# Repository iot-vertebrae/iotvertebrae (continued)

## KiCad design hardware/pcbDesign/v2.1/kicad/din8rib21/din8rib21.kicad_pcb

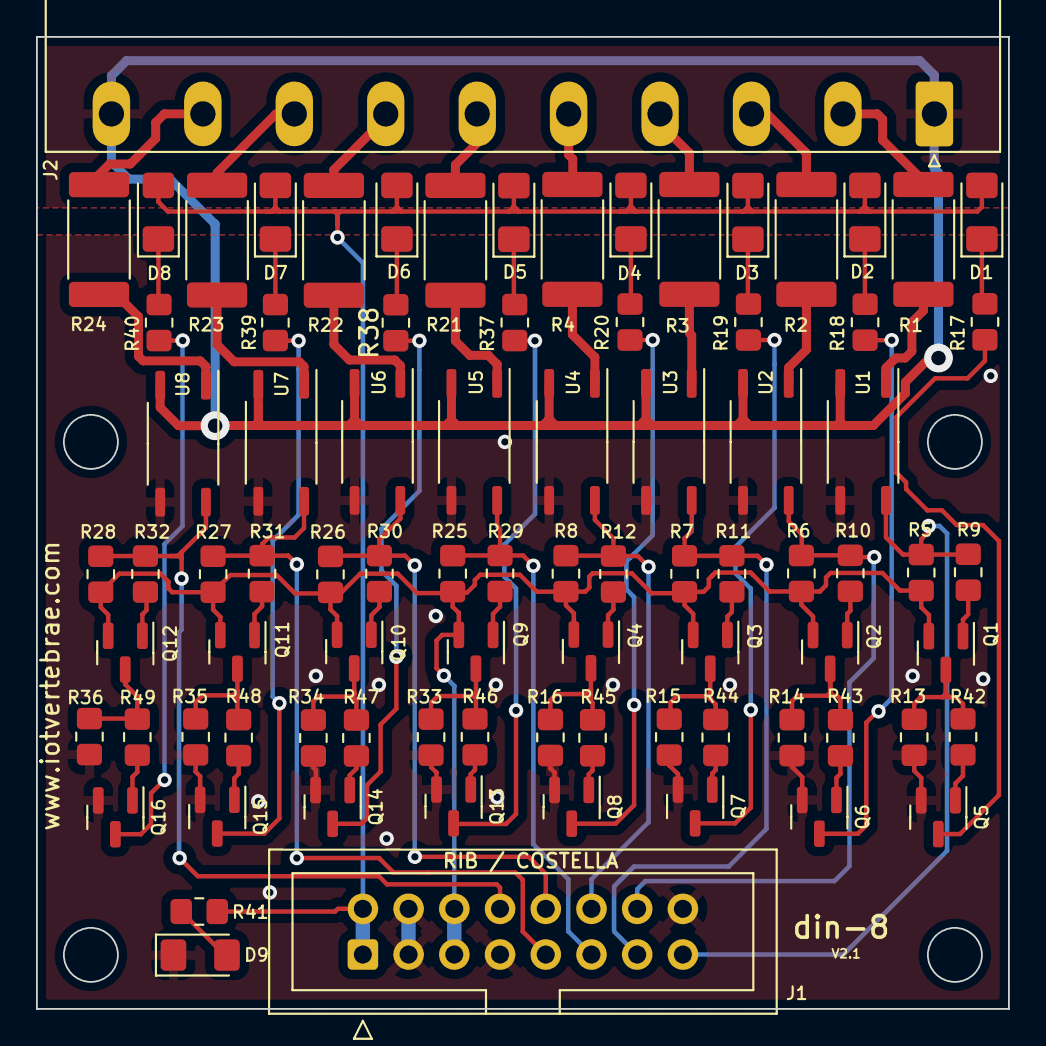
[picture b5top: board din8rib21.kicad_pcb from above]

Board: 2 copper layers, 54.0 x 54.0 mm, 84 parts (0 on the bottom side), 69 nets.

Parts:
D1, D2, D3, D4, D5, D6, D7, D8: GREEN_LED; LED_1206_3216Metric_Pad1.42x1.75mm_HandSolder
D9: RED_LED; LED_1206_3216Metric_Pad1.42x1.75mm_HandSolder
J1: Conn_02x08_Odd_Even; IDC-Header_2x08_P2.54mm_Vertical
J2: Conn_01x10; PhoenixContact_MSTBA_2,5_10-G-5,08_1x10_P5.08mm_Horizontal
Q1, Q2, Q3, Q4, Q9, Q10, Q11, Q12: BC857; SOT-23
Q5, Q6, Q7, Q8, Q13, Q14, Q15, Q16: BC817; SOT-23
R1, R2, R3, R4, R21, R22, R23, R24: 1K2/1W (2512); R_2512_6332Metric_Pad1.40x3.35mm_HandSolder
R5, R6, R7, R8, R9, R10, R11, R12, R25, R26, R27, R28, R29, R30, R31, R32, R42, R43, R44, R45, R46, R47, R48, R49: 3K3; R_0805_2012Metric_Pad1.20x1.40mm_HandSolder
R13, R14, R15, R16, R17, R18, R19, R20, R33, R34, R35, R36, R37, R38, R39, R40, R41: 10K; R_0805_2012Metric_Pad1.20x1.40mm_HandSolder
U1, U2, U3, U4, U5, U6, U7, U8: IS126; SOIC-4_IS126_4.55x3.7mm_P2.54mm

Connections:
+3.3V: J1.5, J1.6, Q1.2 (E), Q2.2 (E), Q3.2 (E), Q4.2 (E), Q9.2 (E), Q10.2 (E), Q11.2 (E), Q12.2 (E), R5.1, R6.1, R7.1, R8.1, R25.1, R26.1, R27.1, R28.1
+24V: D1.2 (A), D2.2 (A), D3.2 (A), D4.2 (A), D5.2 (A), D6.2 (A), D7.2 (A), D8.2 (A), J1.1, J1.2, R41.1
/COM: J2.1, J2.10, U1.2, U2.2, U3.2, U4.2, U5.2, U6.2, U7.2, U8.2
/IN_0: J2.2, R1.1
/IN_1: J2.3, R2.1
/IN_2: J2.4, R3.1
/IN_3: J2.5, R4.1
/IN_4: J2.6, R21.1
/IN_5: J2.7, R22.1
/IN_6: J2.8, R23.1
/IN_7: J2.9, R24.1
/IO_0: J1.15, R5.2, R9.1, U1.4
/IO_1: J1.14, R6.2, R10.1, U2.4
/IO_2: J1.13, R7.2, R11.1, U3.4
/IO_3: J1.12, R8.2, R12.1, U4.4
/IO_4: J1.11, R25.2, R29.1, U5.4
/IO_5: J1.10, R26.2, R30.1, U6.4
/IO_6: J1.9, R27.2, R31.1, U7.4
/IO_7: J1.8, R28.2, R32.1, U8.4
GND: D9.1 (K), J1.3, J1.4, J1.7, J1.16, Q5.2 (E), Q6.2 (E), Q7.2 (E), Q8.2 (E), Q13.2 (E), Q14.2 (E), Q15.2 (E), Q16.2 (E), R13.2, R14.2, R15.2, R16.2, R33.2, R34.2, R35.2, R36.2, U1.3, U2.3, U3.3, U4.3, U5.3, U6.3, U7.3, U8.3
unnamed: D1.1 (K), R17.1
unnamed: D2.1 (K), R18.1
unnamed: D3.1 (K), R19.1
unnamed: D4.1 (K), R20.1
unnamed: D5.1 (K), R37.1
unnamed: D6.1 (K), R38.1
unnamed: D7.1 (K), R39.1
unnamed: D8.1 (K), R40.1
unnamed: D9.2 (A), R41.2
unnamed: Q1.1 (B), R9.2
unnamed: Q1.3 (C), R13.1, R42.1
unnamed: Q2.1 (B), R10.2
unnamed: Q2.3 (C), R14.1, R43.1
unnamed: Q3.1 (B), R11.2
unnamed: Q3.3 (C), R15.1, R44.1
unnamed: Q4.1 (B), R12.2
unnamed: Q4.3 (C), R16.1, R45.1
unnamed: Q5.1 (B), R42.2
unnamed: Q5.3 (C), R17.2
unnamed: Q6.1 (B), R43.2
unnamed: Q6.3 (C), R18.2
unnamed: Q7.1 (B), R44.2
unnamed: Q7.3 (C), R19.2
unnamed: Q8.1 (B), R45.2
unnamed: Q8.3 (C), R20.2
unnamed: Q9.1 (B), R29.2
unnamed: Q9.3 (C), R33.1, R46.1
unnamed: Q10.1 (B), R30.2
unnamed: Q10.3 (C), R34.1, R47.1
unnamed: Q11.1 (B), R31.2
unnamed: Q11.3 (C), R35.1, R48.1
unnamed: Q12.1 (B), R32.2
unnamed: Q12.3 (C), R36.1, R49.1
unnamed: Q13.1 (B), R46.2
unnamed: Q13.3 (C), R37.2
unnamed: Q14.1 (B), R47.2
unnamed: Q14.3 (C), R38.2
unnamed: Q15.1 (B), R48.2
unnamed: Q15.3 (C), R39.2
unnamed: Q16.1 (B), R49.2
unnamed: Q16.3 (C), R40.2
unnamed: R1.2, U1.1
unnamed: R2.2, U2.1
unnamed: R3.2, U3.1
unnamed: R4.2, U4.1
unnamed: R21.2, U5.1
unnamed: R22.2, U6.1
unnamed: R23.2, U7.1
unnamed: R24.2, U8.1

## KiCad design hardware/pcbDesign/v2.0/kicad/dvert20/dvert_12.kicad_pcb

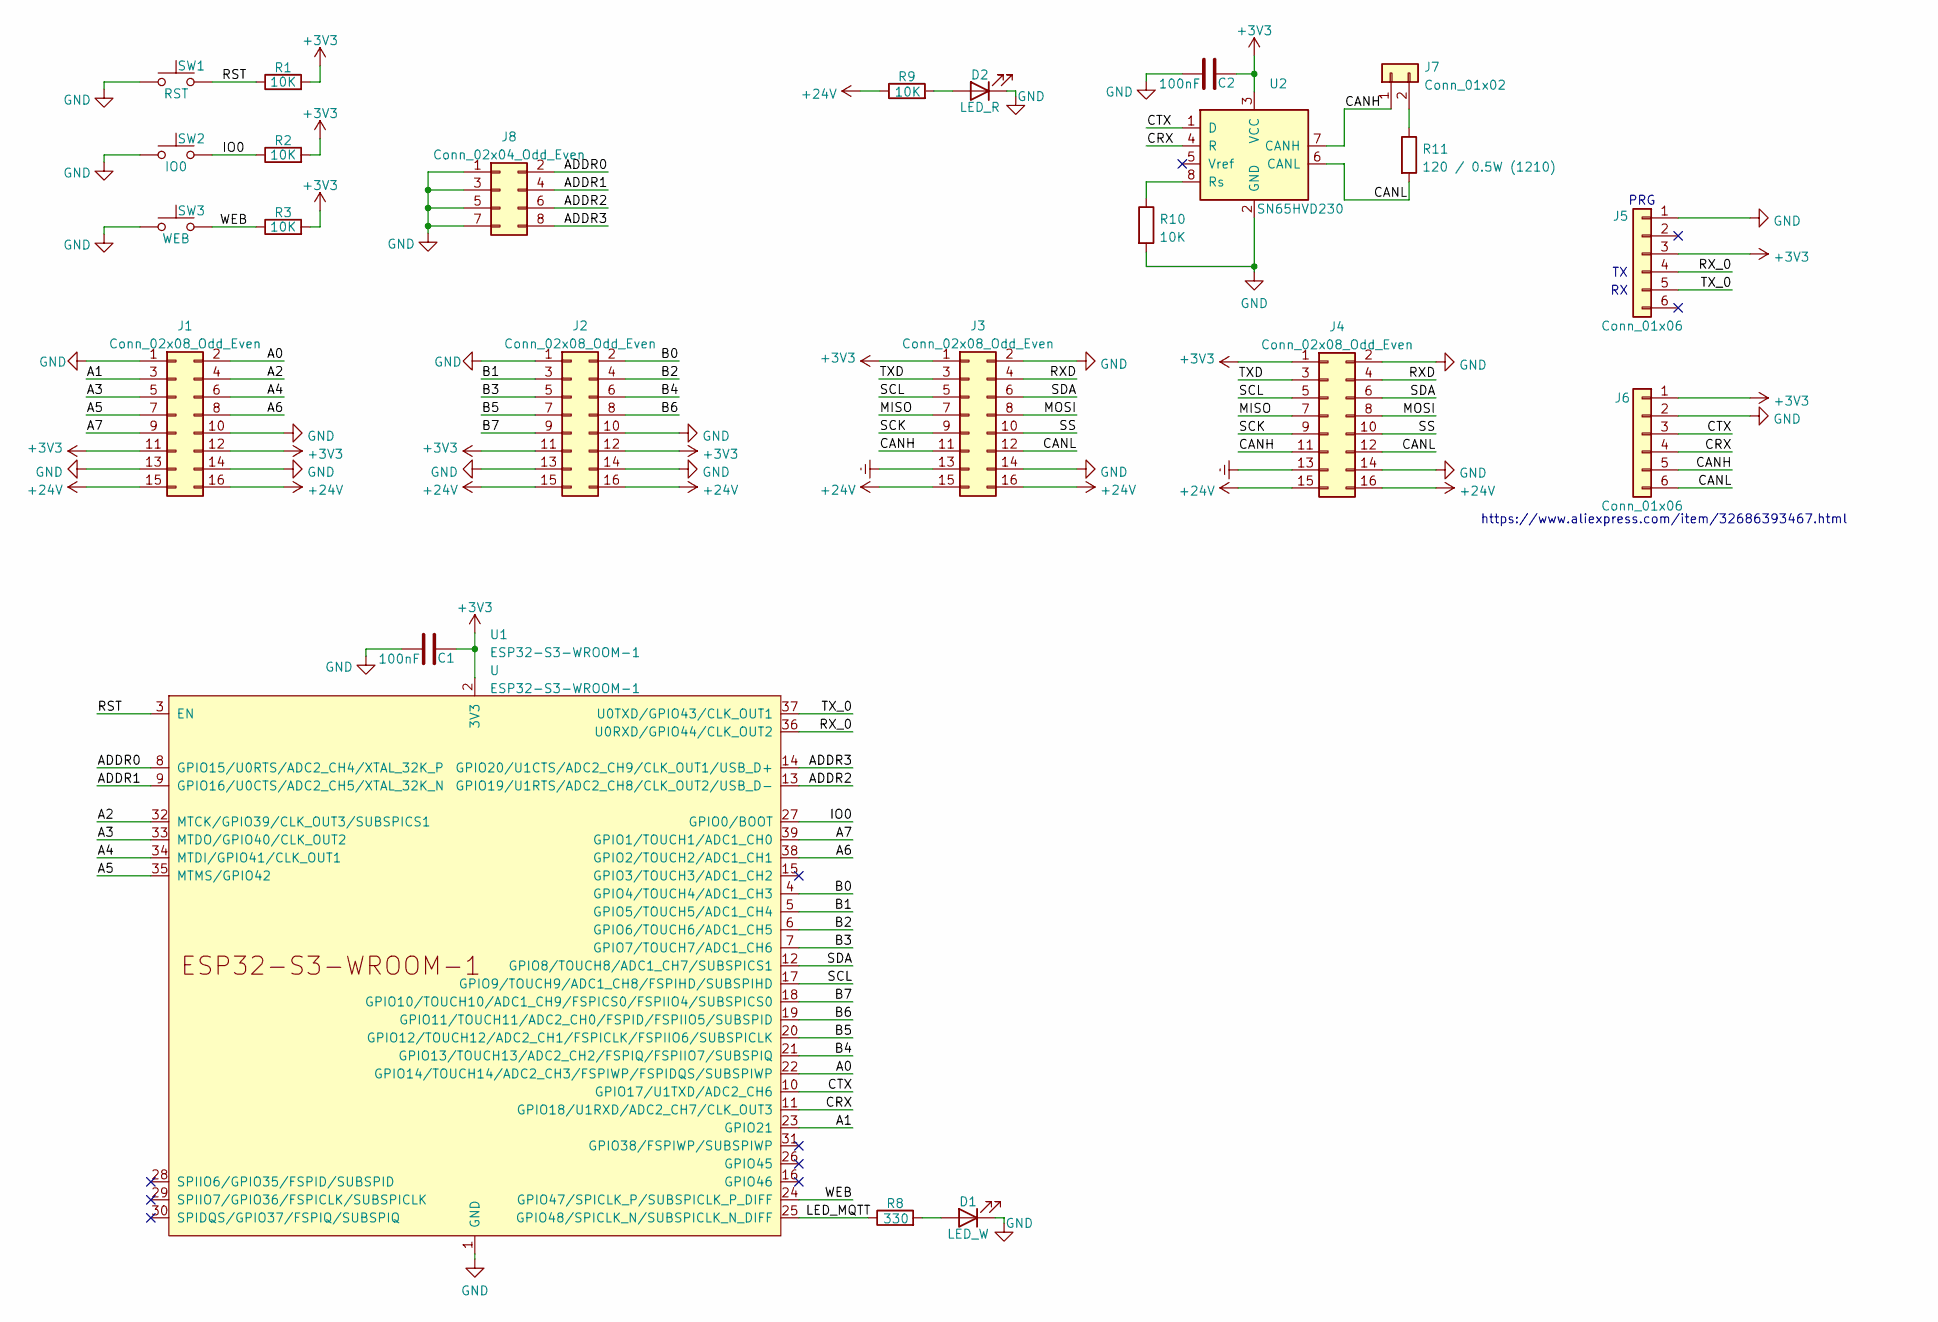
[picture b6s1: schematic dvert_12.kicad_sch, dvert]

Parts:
C1, C2: 100nF; C_0805_2012Metric_Pad1.18x1.45mm_HandSolder
D1: LED_W; LED_1206_3216Metric_Pad1.42x1.75mm_HandSolder
D2: LED_R; LED_1206_3216Metric_Pad1.42x1.75mm_HandSolder
J1, J2, J3, J4: Conn_02x08_Odd_Even; IDC-Header_2x08_P2.54mm_Vertical
J5, J6: Conn_01x06; PinSocket_1x06_P2.54mm_Vertical
J7: Conn_01x02; PinHeader_1x02_P2.54mm_Vertical
J8: Conn_02x04_Odd_Even; PinHeader_2x04_P2.54mm_Vertical
R1, R2, R3, R9, R10: 10K; R_0805_2012Metric_Pad1.20x1.40mm_HandSolder
R8: 330; R_0805_2012Metric_Pad1.20x1.40mm_HandSolder
R11: 120 / 0.5W (1210); R_1210_3225Metric_Pad1.30x2.65mm_HandSolder
SW1: RST; SW_SPST_CK_RS282G05A3
SW2: IO0; SW_SPST_CK_RS282G05A3
SW3: WEB; SW_SPST_CK_RS282G05A3
U1: ESP32-S3-WROOM-1; ESP32-S3-WROOM-1U
U2: SN65HVD230; SOIC-8_3.9x4.9mm_P1.27mm

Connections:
+3V3: C1.2, C2.2, J1.11, J1.12, J2.11, J2.12, J3.1, J4.1, J5.3, J6.1, R1.2, R2.2, R3.2, U1.2 (3V3), U2.3 (VCC)
+24V: J1.15, J1.16, J2.15, J2.16, J3.15, J3.16, J4.15, J4.16, R9.1
/A0: J1.2, U1.22 (GPIO14/TOUCH14/ADC2_CH3/FSPIWP/FSPIDQS/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)
/A1: J1.3, U1.23 (GPIO21)
/A2: J1.4, U1.32 (MTCK/GPIO39/CLK_OUT3/SUBSPICS1)
/A3: J1.5, U1.33 (MTDO/GPIO40/CLK_OUT2)
/A4: J1.6, U1.34 (MTDI/GPIO41/CLK_OUT1)
/A5: J1.7, U1.35 (MTMS/GPIO42)
/A6: J1.8, U1.38 (GPIO2/TOUCH2/ADC1_CH1)
/A7: J1.9, U1.39 (GPIO1/TOUCH1/ADC1_CH0)
/ADDR0: J8.2, U1.8 (GPIO15/U0RTS/ADC2_CH4/XTAL_32K_P)
/ADDR1: J8.4, U1.9 (GPIO16/U0CTS/ADC2_CH5/XTAL_32K_N)
/ADDR2: J8.6, U1.13 (GPIO19/U1RTS/ADC2_CH8/CLK_OUT2/USB_D-)
/ADDR3: J8.8, U1.14 (GPIO20/U1CTS/ADC2_CH9/CLK_OUT1/USB_D+)
/B0: J2.2, U1.4 (GPIO4/TOUCH4/ADC1_CH3)
/B1: J2.3, U1.5 (GPIO5/TOUCH5/ADC1_CH4)
/B2: J2.4, U1.6 (GPIO6/TOUCH6/ADC1_CH5)
/B3: J2.5, U1.7 (GPIO7/TOUCH7/ADC1_CH6)
/B4: J2.6, U1.21 (GPIO13/TOUCH13/ADC2_CH2/FSPIQ/FSPIIO7/S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)
/B5: J2.7, U1.20 (GPIO12/TOUCH12/ADC2_CH1/FSPICLK/FSPIIO6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)
/B6: J2.8, U1.19 (GPIO11/TOUCH11/ADC2_CH0/FSPID/FSPIIO5/S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)
/B7: J2.9, U1.18 (GPIO10/TOUCH10/ADC1_CH9/FSPICS0/FSPIIO4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)
/CANH: J3.11, J4.11, J6.5, J7.1, U2.7 (CANH)
/CANL: J3.12, J4.12, J6.6, R11.2, U2.6 (CANL)
/CRX: J6.4, U1.11 (GPIO18/U1RXD/ADC2_CH7/CLK_OUT3), U2.4 (R)
/CTX: J6.3, U1.10 (GPIO17/U1TXD/ADC2_CH6), U2.1 (D)
/IO0: R2.1, SW2.2, U1.27 (GPIO0/BOOT)
/LED_MQTT: R8.1, U1.25 (GPIO48/SPICLK_N/SUBSPICLK_N_DIFF)
/MISO: J3.7, J4.7
/MOSI: J3.8, J4.8
/RST: R1.1, SW1.2, U1.3 (EN)
/RXD: J3.4, J4.4
/RX_0: J5.4, U1.36 (U0RXD/GPIO44/CLK_OUT2)
/SCK: J3.9, J4.9
/SCL: J3.5, J4.5, U1.17 (GPIO9/TOUCH9/ADC1_CH8/FSPIHD/SUBSPIHD)
/SDA: J3.6, J4.6, U1.12 (GPIO8/TOUCH8/ADC1_CH7/SUBSPICS1)
/SS: J3.10, J4.10
/TXD: J3.3, J4.3
/TX_0: J5.5, U1.37 (U0TXD/GPIO43/CLK_OUT1)
/WEB: R3.1, SW3.2, U1.24 (GPIO47/SPICLK_P/SUBSPICLK_P_DIFF)
Earth: J3.13, J4.13
GND: C1.1, C2.1, D1.1 (K), D2.1 (K), J1.1, J1.10, J1.13, J1.14, J2.1, J2.10, J2.13, J2.14, J3.2, J3.14, J4.2, J4.14, J5.1, J6.2, J8.1, J8.3, J8.5, J8.7, R10.2, SW1.1, SW2.1, SW3.1, U1.1 (GND), U1.40 (GND), U1.41 (GND), U2.2 (GND)
unnamed: D1.2 (A), R8.2
unnamed: D2.2 (A), R9.2
unnamed: J7.2, R11.1
unnamed: R10.1, U2.8 (Rs)

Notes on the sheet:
https://www.aliexpress.com/item/32686393467.html
PRG

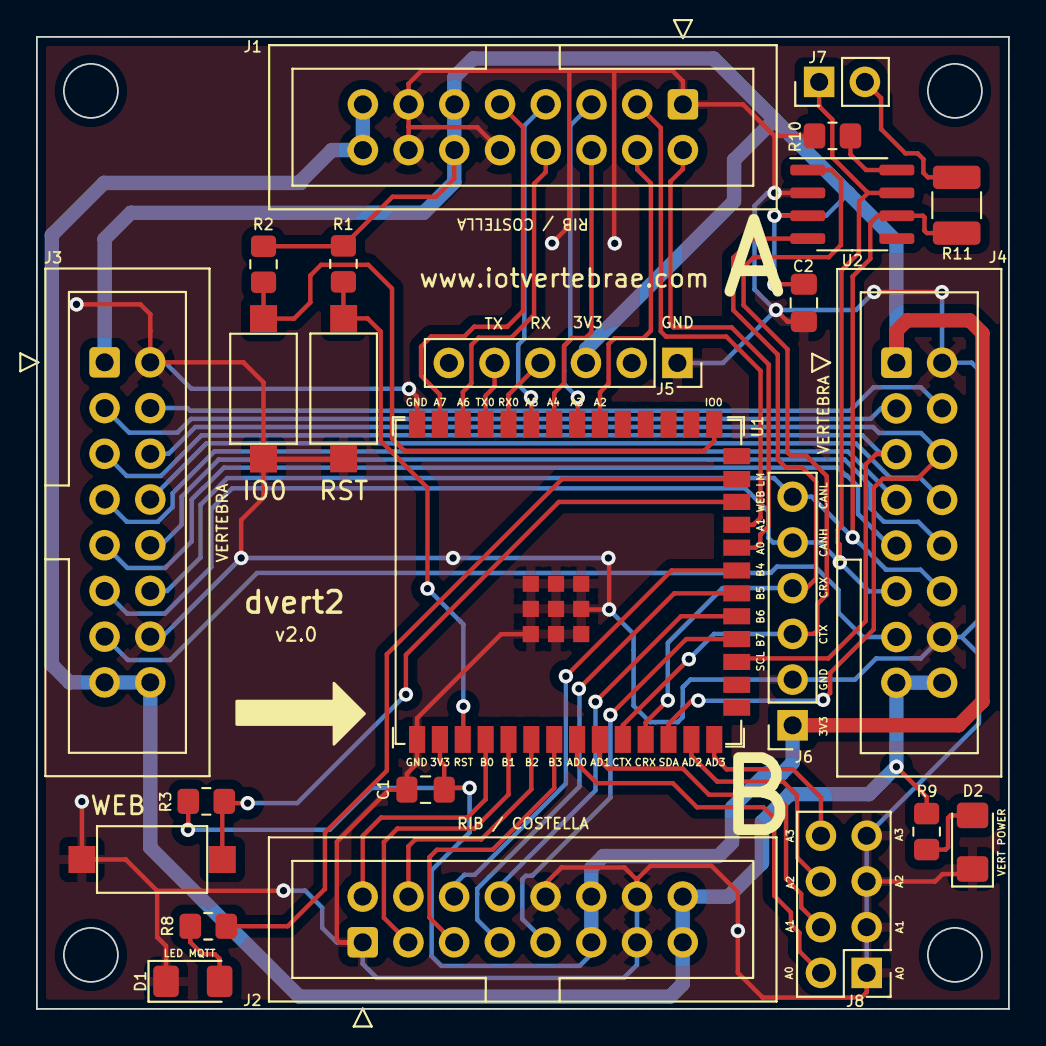
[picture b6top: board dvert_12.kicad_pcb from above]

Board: 2 copper layers, 54.0 x 54.0 mm, 24 parts (0 on the bottom side), 46 nets.

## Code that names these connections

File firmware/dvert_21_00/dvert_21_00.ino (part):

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#define DVERT_VERSION    0x01
#define DVERT_SUBVERSION 0x00

#define ADDR0 20
#define ADDR1 19
#define ADDR2 16
#define ADDR3 15
#define LED_MQTT 48
#define A0 14
#define A1 21
#define A2 39
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#define B7 10

#define RX_PIN 18
#define CRX RX_PIN
#define TX_PIN 17
#define CTX TX_PIN

#define REG_CFG   0x00
#define REG_RD    0x01
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byte byLastReadNumber,byRibCfg;

void vSetupAddr(){
  pinMode(LED_MQTT, OUTPUT);
  pinMode(ADDR0, INPUT_PULLUP);
  pinMode(ADDR1, INPUT_PULLUP);
  pinMode(ADDR2, INPUT_PULLUP);
  pinMode(ADDR3, INPUT_PULLUP); 
}

void vReadEeprom(int nQ){
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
